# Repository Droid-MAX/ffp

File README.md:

# FFP: Flash/FPGA Programmer

FFP is a dead-simple USB to bidirectional SPI bridge for programming iCE40
FPGAs and their SPI flash. The hardware is an STM32F042 and not much else.
Firmware and host software is written in Rust.

The firmware additionally supports SWD via the CMSIS-DAP v1 protocol,
so many debuggers such as [probe-rs], [OpenOCD], and [pyOCD] are able to
use an FFP to debug and program Cortex-M and other microcontrollers.

[probe-rs]: https://probe.rs
[OpenOCD]: http://openocd.org
[pyOCD]: https://github.com/mbedmicro/pyOCD

See [software/](software/) for the host-side software, [firmware/](firmware/)
for the embedded device firmware, and [hardware/](hardware/ffp/) for the
hardware design files.

## Pinout

The FFP r1 hardware uses a 5x2 pin 0.05"-pitch connector, which is also
commonly used for Cortex family microcontrollers for SWD and JTAG. The pinout
is deliberately compatible (though note `RESET` is moved) to allow hardware
reuse and for compatibility with tools such as TagConnect cables.

```ascii
          ______
    3v3 --|1  2|-- FLASH DI / FPGA DO / SWDIO
    GND --|3  4|-- CLK / SWCLK
    GND --|5  6|-- CS / SWO
   NULL --|7  8|-- FPGA nRST
    GND --|9 10|-- FLASH DO / FPGA DI / nRESET
          ------

```

This is the same pinout used by
[amp_flashprog](https://github.com/adamgreig/amp_flashprog), a custom firmware
for [Black Magic Probes](https://github.com/blacksphere/blackmagic) to bitbang
SPI to the same ends.

## Licence

Software and firmware is licensed under either of

* Apache License, Version 2.0 ([LICENSE-APACHE](LICENSE-APACHE) or
  http://www.apache.org/licenses/LICENSE-2.0)
* MIT license ([LICENSE-MIT](LICENSE-MIT) or http://opensource.org/licenses/MIT)

at your option.

Hardware design files are licensed under the Creative Commons Attribution
license ([CC-BY](https://creativecommons.org/licenses/by/4.0/)).

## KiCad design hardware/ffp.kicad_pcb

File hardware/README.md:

# FFP: Flash/FPGA Programmer

FFP is a dead-simple USB to bidirectional SPI bridge for programming iCE40
FPGAs and their SPI flash. The hardware is an STM32F042 and not much else.
Firmware and host software is written in Rust.

See [software/](software/) for the host-side software, [firmware/](firmware/)
for the embedded device firmware, and [hardware/](hardware/ffp/) for the
hardware design files.

## Pinout

The FFP r1 hardware uses a 5x2 pin 0.05"-pitch connector, which is also
commonly used for Cortex family microcontrollers for SWD and JTAG. The pinout
is deliberately compatible (though note `RESET` is moved) to allow hardware
reuse and for compatibility with tools such as TagConnect cables. It would
also be possible to add SWD support to FFP without changing the hardware,
permitting programming of Cortex-M devices.

```ascii
          ______
    3v3 --|1  2|-- FLASH DI / FPGA DO
    GND --|3  4|-- CLK
    GND --|5  6|-- CS
        x-|7  8|-- FPGA nRST
    GND --|9 10|-- FLASH DO / FPGA DI
          ------

```

This is the same pinout used by
[amp_flashprog](https://github.com/adamgreig/amp_flashprog), a custom firmware
for [Black Magic Probes](https://github.com/blacksphere/blackmagic) to bitbang
SPI to the same ends.

## Licence

Software and firmware is licensed under either of

* Apache License, Version 2.0 ([LICENSE-APACHE](LICENSE-APACHE) or
  http://www.apache.org/licenses/LICENSE-2.0)
* MIT license ([LICENSE-MIT](LICENSE-MIT) or http://opensource.org/licenses/MIT)

at your option.

Hardware design files are licensed under the Creative Commons Attribution
license ([CC-BY](https://creativecommons.org/licenses/by/4.0/)).

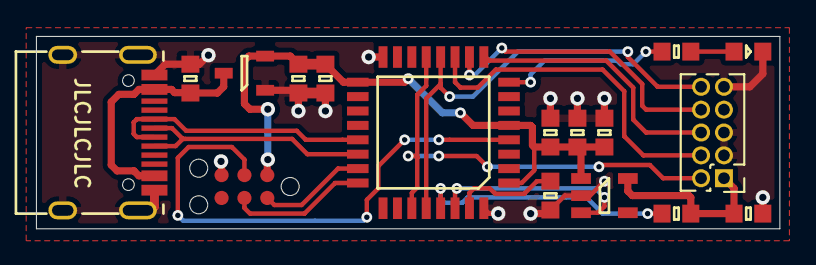
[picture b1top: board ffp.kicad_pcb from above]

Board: 2 copper layers, 41.3 x 10.7 mm, 17 parts (0 on the bottom side), 19 nets.

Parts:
C1, C2, C3, C4, C7: 100n; 0603
C5, C6: 1µ; 0603
D1: LED; 0603-LED
IC1: STM32F042K6T7; LQFP-32
IC2: MCP1700; SOT-23
IC3: MIC2004-0_5YM5; SOT-23-5
J2: USB_C_Receptacle_USB2.0; USB-C_16Pin
J3: PROG; PinHeader_2x05_P1.27mm_Vertical
P1: SWD_TC; TC2030-NL
R1, R2, R3: 10k; 0603

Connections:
3v3: C1.1, C2.1, C3.1, C4.1, C6.1, IC1.1, IC1.5, IC1.17, IC2.2, IC3.1, P1.1
5v: C5.1, IC2.3, J2.A4, J2.B4
/FLASH_SI: IC1.13, IC1.27, J3.2
/FLASH_SO: IC1.12, IC1.28, J3.10
/FLASH_~CS: IC1.9, J3.6
/FPGA_~RST: IC1.10, J3.8
/SCK: IC1.11, J3.4
/TGT_3v3: C7.1, IC3.5, J3.1, R2.1
/TPWR_EN: IC1.30, IC3.3
/USB_DM: IC1.21, J2.A7, J2.B7
/USB_DP: IC1.22, J2.A6, J2.B6
/~RST: IC1.4, P1.3
GND: C1.2, C2.2, C3.2, C4.2, C5.2, C6.2, C7.2, D1.1, IC1.16, IC1.32, IC2.1, IC3.2, J2.A1, J2.B1, J2.S1, J3.3, J3.5, J3.9, P1.5, R1.2
unnamed: D1.2, R3.1
unnamed: IC1.8, R3.2
unnamed: IC1.23, P1.2
unnamed: IC1.24, P1.4
unnamed: IC1.29, R2.2
unnamed: IC1.31, R1.1

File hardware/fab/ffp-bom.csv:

"Comment","Description","Designator","Footprint","LibRef","Pins","Quantity","PartNumber","url",
"1µ","desc","C6,C5,","0603","libref","2","2","","",
"100n","desc","C7,C4,C3,C2,C1,","0603","libref","2","5","","",
"LED","desc","D1,","0603-LED","libref","2","1","","",
"STM32F042K6T7","desc","IC1,","LQFP-32","libref","32","1","","https://www.st.com/resource/en/datasheet/stm32f042k6.pdf",
"MCP1700","desc","IC2,","SOT-23","libref","3","1","","",
"MIC2004-0_5YM5","desc","IC3,","SOT-23-5","libref","5","1","","http://ww1.microchip.com/downloads/en/DeviceDoc/mic20xx.pdf",
"PROG","desc","J3,","FTSH-105-01-L-DV-K","libref","10","1","","",
"10k","desc","R3,R2,R1,","0603","libref","2","3","","",
"Through Hole Items ",
"USB_C_Receptacle_USB2.0","desc","J2,","USB-C_16Pin","libref","18","1","","https://www.usb.org/sites/default/files/documents/usb_type-c.zip",
"SWD_TC","desc","P1,","TC2030-NL","libref","9","1","","",

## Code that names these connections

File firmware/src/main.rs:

// Copyright 2019 Adam Greig
// Dual licensed under the Apache 2.0 and MIT licenses.

#![no_std]
#![no_main]

extern crate panic_halt;
use cortex_m_rt::{entry, pre_init};

pub mod hal;
pub mod app;

use app::App;

#[pre_init]
unsafe fn pre_init() {
    // Check if we should jump to system bootloader.
    //
    // When we receive the BOOTLOAD command over USB,
    // we write a flag to a static and reset the chip,
    // and `bootload::check()` will jump to the system
    // memory bootloader if the flag is present.
    //
    // It must be called from pre_init as otherwise the
    // flag is overwritten when statics are initialised.
    hal::bootload::check();
}

#[entry]
fn main() -> ! {
    // Obtain all required HAL instances
    let flash = hal::flash::Flash::new(stm32ral::flash::Flash::take().unwrap());
    let rcc = hal::rcc::RCC::new(stm32ral::rcc::RCC::take().unwrap(),
                                 stm32ral::crs::CRS::take().unwrap());
    let nvic = hal::nvic::NVIC::new(stm32ral::nvic::NVIC::take().unwrap(),
                                    stm32ral::scb::SCB::take().unwrap());
    let dma = hal::dma::DMA::new(stm32ral::dma1::DMA1::take().unwrap());
    let gpioa = hal::gpio::GPIO::new(stm32ral::gpio::GPIOA::take().unwrap());
    let gpiob = hal::gpio::GPIO::new(stm32ral::gpio::GPIOB::take().unwrap());
    let mut spi = hal::spi::SPI::new(stm32ral::spi::SPI1::take().unwrap());
    let mut usb = hal::usb::USB::new(stm32ral::usb::USB::take().unwrap());

    // Define pinout
    let pins = hal::gpio::Pins {
        led: gpioa.pin(2),
        cs: gpioa.pin(3),
        fpga_rst: gpioa.pin(4),
        sck: gpioa.pin(5),
        flash_so: gpioa.pin(6),
        flash_si: gpioa.pin(7),
        fpga_so: gpiob.pin(4),
        fpga_si: gpiob.pin(5),
        tpwr_det: gpiob.pin(6),
        tpwr_en: gpiob.pin(7),
    };

    // Create App instance with the HAL instances
    let mut app = App::new(&flash, &rcc, &nvic, &dma, &pins, &mut spi, &mut usb);

    // Initialise application, including system peripherals
    app.setup();

    loop {
        // Process events
        app.poll();
    }
}

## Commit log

2020-03-27 replace usb4085 package of type-c interface to 16pin package
2020-03-28 adjust the border and remove the top copper
2020-03-28 update gerber files
2020-03-28 add dimension for pcb file
2020-03-28 remove duplicate files
2020-03-28 fix dimension layer to F.Fab
2020-03-29 detail adjustment
2020-03-29 replated copper to the top and updated gerber files
2020-03-31 replaced the connector with a dual row 5pin header with 1.27mm pitch
2020-04-06 optimized USB differential line routing
2020-04-09 fix some detail problems on F.Fab
2020-04-11 synchronized upstream changes
2020-04-20 updated ffp_pcb.jpg

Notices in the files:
hardware/ffp.kicad_pcb:
Licensed under Creative Commons Attribution 4.0
